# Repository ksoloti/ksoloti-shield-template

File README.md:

# Ksoloti Core Shield Kicad Template

Shield Template Project for Ksoloti Core v0.5+ and Kicad 6+. You can use this as a starting point to design your own shield.

## Installation Instructions

Clone this repo to your User Templates directory. It will then show up under the `User Templates` tab when you create a `New Project from Template`. You can find the default User Templates directory by checking the `KICAD_USER_TEMPLATE_DIR` variable in `Preferences > Configure Paths...` or by navigating to the `User Templates` tab in the Project Template Selector window after you've selected `New Project from Template` in the file menu.

Example Locations (might differ depending on your Kicad version):
 * Windows: `C:\Users\<user name>\Documents\kicad\<version>\template\`
 * Mac: `/Users/<user name>/Documents/kicad/<version>/template/`
 * Linux: `/home/<username>/.local/share/kicad/<version>/template/`

Alternatively, clone the project any location you wish and then browse to it in the `Project Template Selector` window on the `User Templates` tab. 

## About

The Ksoloti Core plugs into the bottom of the template and all its relevant pins are brought out to the sockets of the template.

All pins in this template have been realized as single-pin footprints so you can delete whichever pins you don't need and claim back some space for your design.

The included mounting holes are also optional. You can delete them if they conflict with your part placement (the headers make a solid enough connection), although it is recommended you keep the two top (north) holes to maintain a solid connection when plugging your USB cables. M3 standoffs with 12mm length fit well here.

## Library & Footprints

The template/project has its own little library of parts in case you're looking for something to get started with. Most of these parts are available via Thonk.
* pot, dual pot
* switch, switch with LED, encoder with switch
* 6.35mm TRS audio jack, 3.5mm TRS audio jack
* DIN-5 MIDI socket
* 3mm LED, 3mm bicolor LED (3 pins, AKA)
* 1.3" OLED display (pinout: GND, VCC, SCL, SDA. `BE CAREFUL: pinout varies on these cheap OLEDs! Confirm your OLEDs pinout and adjust the footprint accordingly.`

## Top view

## Bottom view

## Bottom view with Core plugged in

## Parts library

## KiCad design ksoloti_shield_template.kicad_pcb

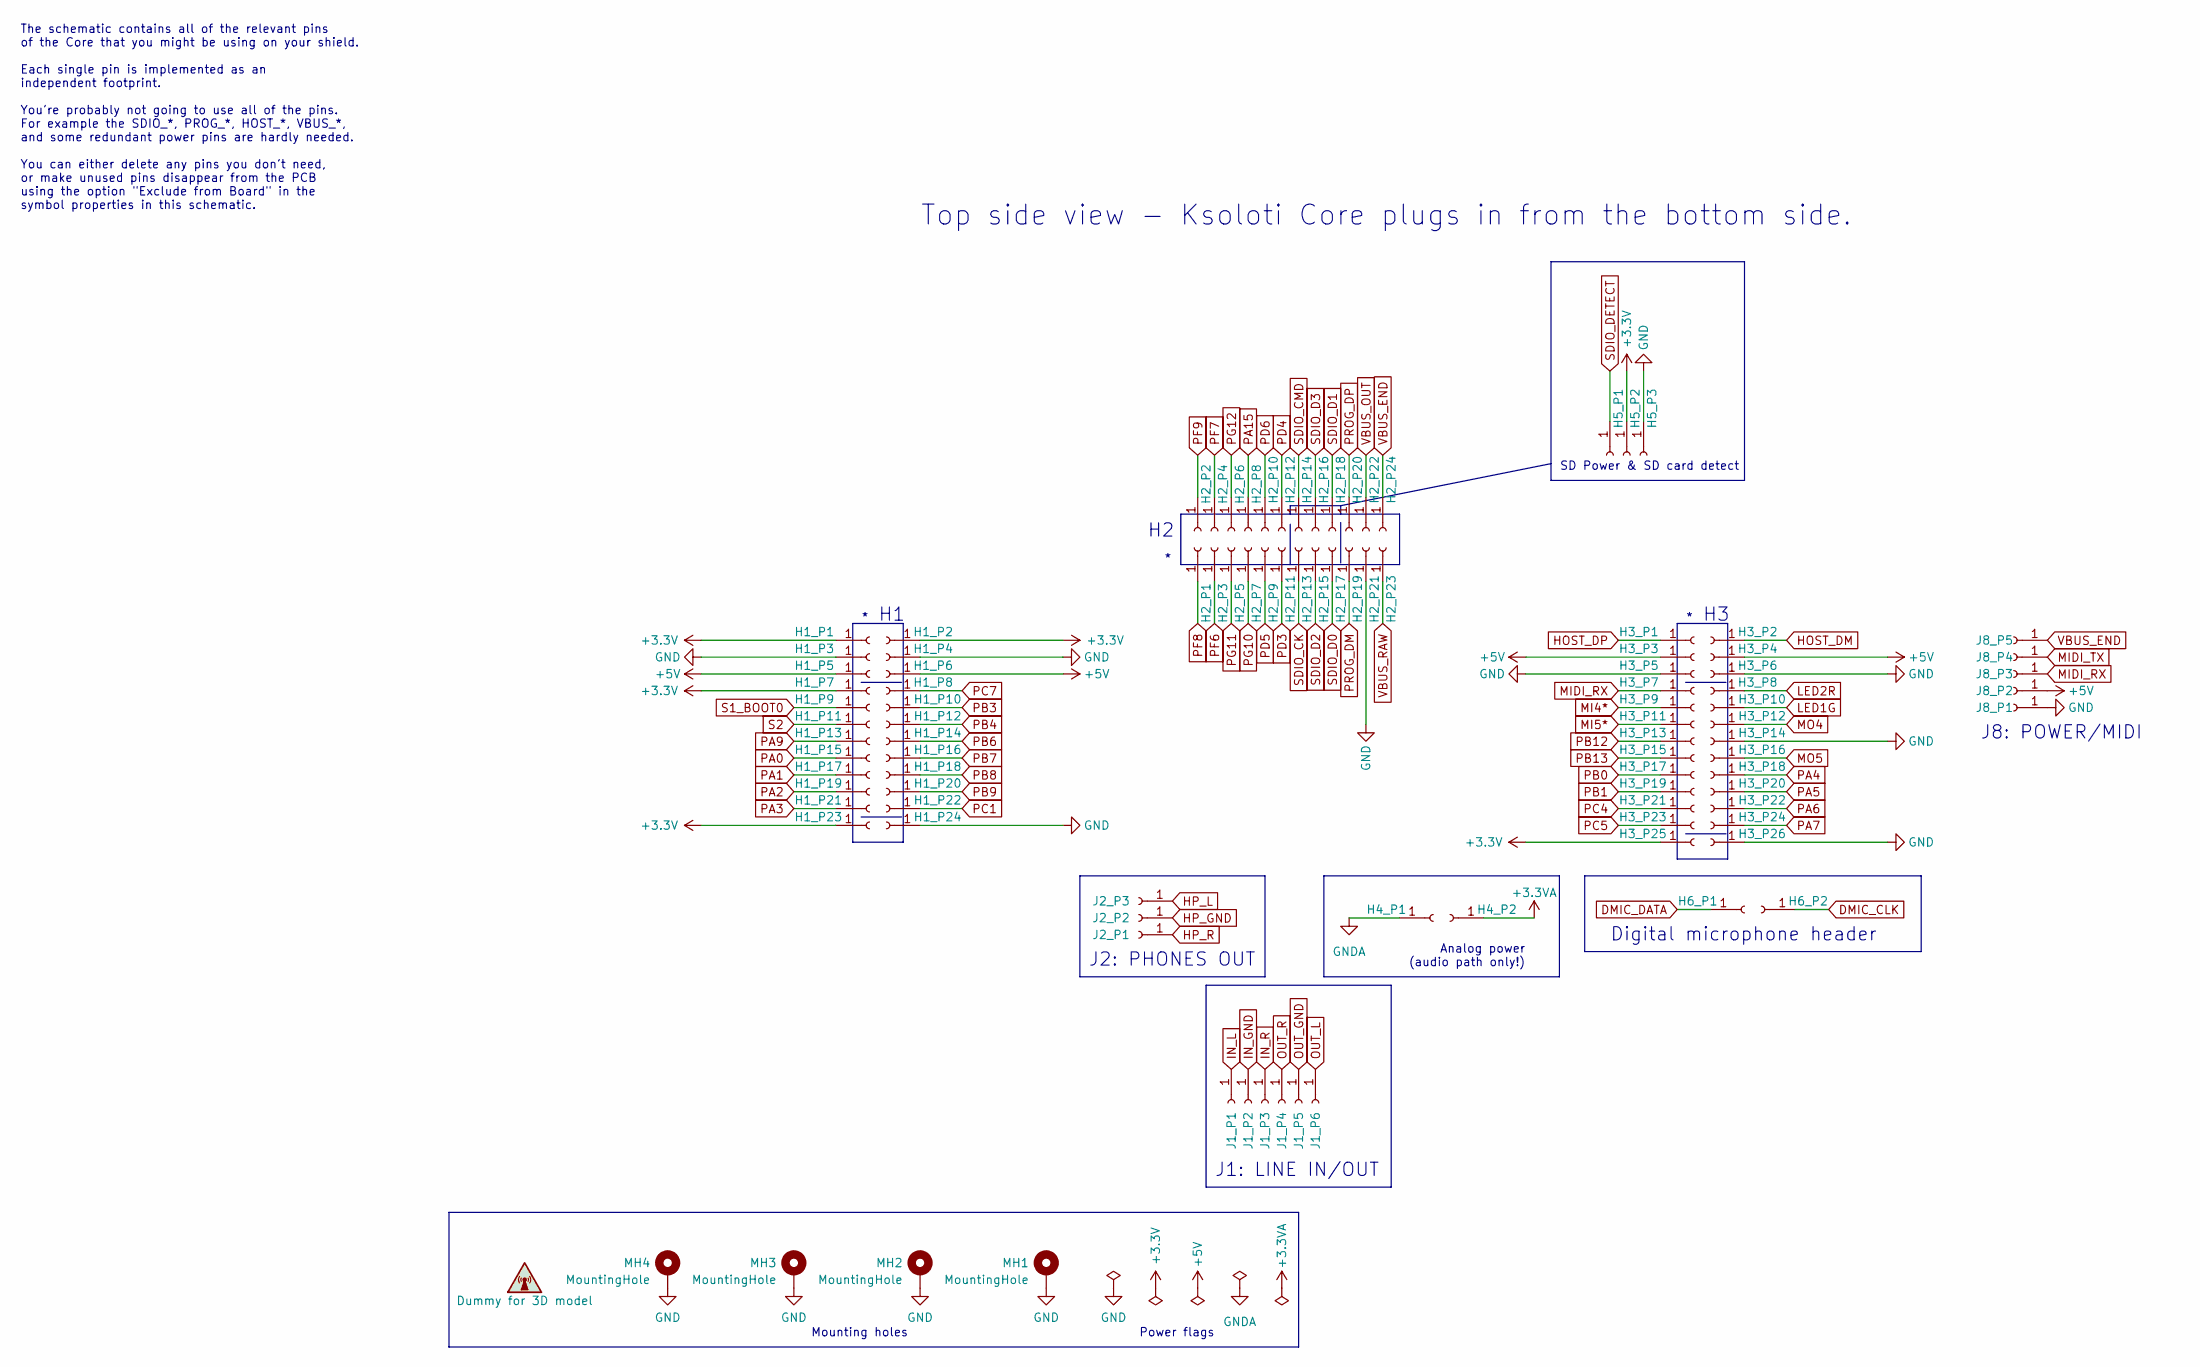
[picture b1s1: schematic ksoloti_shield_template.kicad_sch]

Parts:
DUMMY1: Dummy for 3D model
H1_P1: +3.3V; PinSocket_1x01_P2.54mm_Vertical_smcrt_sqr
H1_P2, H1_P7, H1_P23, H3_P25, H5_P2: +3.3V; PinSocket_1x01_P2.54mm_Vertical_smcrt_round
H1_P3, H1_P4, H1_P24, H2_P21, H3_P5, H3_P6, H3_P14, H3_P26, H5_P3: GND; PinSocket_1x01_P2.54mm_Vertical_smcrt_round
H1_P5, H1_P6, H3_P3, H3_P4: +5V; PinSocket_1x01_P2.54mm_Vertical_smcrt_round
H1_P8: PC7; PinSocket_1x01_P2.54mm_Vertical_smcrt_round
H1_P9: S1_BOOT0; PinSocket_1x01_P2.54mm_Vertical_smcrt_round
H1_P10: PB3; PinSocket_1x01_P2.54mm_Vertical_smcrt_round
H1_P11: S2; PinSocket_1x01_P2.54mm_Vertical_smcrt_round
H1_P12: PB4; PinSocket_1x01_P2.54mm_Vertical_smcrt_round
H1_P13: PA9; PinSocket_1x01_P2.54mm_Vertical_smcrt_round
H1_P14: PB6; PinSocket_1x01_P2.54mm_Vertical_smcrt_round
H1_P15: PA0; PinSocket_1x01_P2.54mm_Vertical_smcrt_round
H1_P16: PB7; PinSocket_1x01_P2.54mm_Vertical_smcrt_round
H1_P17: PA1; PinSocket_1x01_P2.54mm_Vertical_smcrt_round
H1_P18: PB8; PinSocket_1x01_P2.54mm_Vertical_smcrt_round
H1_P19: PA2; PinSocket_1x01_P2.54mm_Vertical_smcrt_round
H1_P20: PB9; PinSocket_1x01_P2.54mm_Vertical_smcrt_round
H1_P21: PA3; PinSocket_1x01_P2.54mm_Vertical_smcrt_round
H1_P22: PC1; PinSocket_1x01_P2.54mm_Vertical_smcrt_round
H2_P1: PF8; PinSocket_1x01_P2.54mm_Vertical_smcrt_sqr
H2_P2: PF9; PinSocket_1x01_P2.54mm_Vertical_smcrt_round
H2_P3: PF6; PinSocket_1x01_P2.54mm_Vertical_smcrt_round
H2_P4: PF7; PinSocket_1x01_P2.54mm_Vertical_smcrt_round
H2_P5: PG11; PinSocket_1x01_P2.54mm_Vertical_smcrt_round
H2_P6: PG12; PinSocket_1x01_P2.54mm_Vertical_smcrt_round
H2_P7: PG10; PinSocket_1x01_P2.54mm_Vertical_smcrt_round
H2_P8: PA15; PinSocket_1x01_P2.54mm_Vertical_smcrt_round
H2_P9: PD5; PinSocket_1x01_P2.54mm_Vertical_smcrt_round
H2_P10: PD6; PinSocket_1x01_P2.54mm_Vertical_smcrt_round
H2_P11: PD3; PinSocket_1x01_P2.54mm_Vertical_smcrt_round
H2_P12: PD4; PinSocket_1x01_P2.54mm_Vertical_smcrt_round
H2_P13: SDIO_CK; PinSocket_1x01_P2.54mm_Vertical_smcrt_round
H2_P14: SDIO_CMD; PinSocket_1x01_P2.54mm_Vertical_smcrt_round
H2_P15: SDIO_D2; PinSocket_1x01_P2.54mm_Vertical_smcrt_round
H2_P16: SDIO_D3; PinSocket_1x01_P2.54mm_Vertical_smcrt_round
H2_P17: SDIO_D0; PinSocket_1x01_P2.54mm_Vertical_smcrt_round
H2_P18: SDIO_D1; PinSocket_1x01_P2.54mm_Vertical_smcrt_round
H2_P19: PROG_DM; PinSocket_1x01_P2.54mm_Vertical_smcrt_round
H2_P20: PROG_DP; PinSocket_1x01_P2.54mm_Vertical_smcrt_round
H2_P22: VBUS_OUT; PinSocket_1x01_P2.54mm_Vertical_smcrt_round
H2_P23: VBUS_RAW; PinSocket_1x01_P2.54mm_Vertical_smcrt_round
H2_P24: VBUS_END; PinSocket_1x01_P2.54mm_Vertical_smcrt_round
H3_P1: HOST_DP; PinSocket_1x01_P2.54mm_Vertical_smcrt_sqr
H3_P2: HOST_DM; PinSocket_1x01_P2.54mm_Vertical_smcrt_round
H3_P7: MIDI_RX; PinSocket_1x01_P2.54mm_Vertical_smcrt_round
H3_P8: LED2R; PinSocket_1x01_P2.54mm_Vertical_smcrt_round
H3_P9: MI4; PinSocket_1x01_P2.54mm_Vertical_smcrt_round
H3_P10: LED1G; PinSocket_1x01_P2.54mm_Vertical_smcrt_round
H3_P11: MI5; PinSocket_1x01_P2.54mm_Vertical_smcrt_round
H3_P12: MO4; PinSocket_1x01_P2.54mm_Vertical_smcrt_round
H3_P13: PB12; PinSocket_1x01_P2.54mm_Vertical_smcrt_round
H3_P15: PB13; PinSocket_1x01_P2.54mm_Vertical_smcrt_round
H3_P16: MO5; PinSocket_1x01_P2.54mm_Vertical_smcrt_round
H3_P17: PB0; PinSocket_1x01_P2.54mm_Vertical_smcrt_round
H3_P18: PA4; PinSocket_1x01_P2.54mm_Vertical_smcrt_round
H3_P19: PB1; PinSocket_1x01_P2.54mm_Vertical_smcrt_round
H3_P20: PA5; PinSocket_1x01_P2.54mm_Vertical_smcrt_round
H3_P21: PC4; PinSocket_1x01_P2.54mm_Vertical_smcrt_round
H3_P22: PA6; PinSocket_1x01_P2.54mm_Vertical_smcrt_round
H3_P23: PC5; PinSocket_1x01_P2.54mm_Vertical_smcrt_round
H3_P24: PA7; PinSocket_1x01_P2.54mm_Vertical_smcrt_round
H4_P1: GNDA; PinSocket_1x01_P2.54mm_Vertical_smcrt_sqr
H4_P2: +3.3VA; PinSocket_1x01_P2.54mm_Vertical_smcrt_round
H5_P1: SDIO_DETECT; PinSocket_1x01_P2.54mm_Vertical_smcrt_sqr
H6_P1: DMIC_DATA; PinSocket_1x01_P2.54mm_Vertical_smcrt_round
H6_P2: DMIC_CLK; PinSocket_1x01_P2.54mm_Vertical_smcrt_round
J1_P1: IN_L; PinSocket_1x01_P2.54mm_Vertical_smcrt_sqr
J1_P2: IN_GND; PinSocket_1x01_P2.54mm_Vertical_smcrt_round
J1_P3: IN_R; PinSocket_1x01_P2.54mm_Vertical_smcrt_round
J1_P4: OUT_R; PinSocket_1x01_P2.54mm_Vertical_smcrt_round
J1_P5: OUT_GND; PinSocket_1x01_P2.54mm_Vertical_smcrt_round
J1_P6: OUT_L; PinSocket_1x01_P2.54mm_Vertical_smcrt_round
J2_P1: HP_R; PinSocket_1x01_P2.54mm_Vertical_smcrt_sqr
J2_P2: HP_GND; PinSocket_1x01_P2.54mm_Vertical_smcrt_round
J2_P3: HP_L; PinSocket_1x01_P2.54mm_Vertical_smcrt_round
J8_P1: GND; PinSocket_1x01_P2.54mm_Vertical_smcrt_sqr
J8_P2: +5V; PinSocket_1x01_P2.54mm_Vertical_smcrt_round
J8_P3: MIDI_RX*; PinSocket_1x01_P2.54mm_Vertical_smcrt_round
J8_P4: MIDI_TX; PinSocket_1x01_P2.54mm_Vertical_smcrt_round
J8_P5: VBUS_END; PinSocket_1x01_P2.54mm_Vertical_smcrt_round
MH1, MH2, MH3, MH4: MountingHole; MountingHole_3.2mm_M3_Pad_Via_tight

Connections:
+3.3V: H1_P1.1, H1_P2.1, H1_P7.1, H1_P23.1, H3_P25.1, H5_P2.1
+3.3VA: H4_P2.1
+5V: H1_P5.1, H1_P6.1, H3_P3.1, H3_P4.1, J8_P2.1
DMIC_CLK: H6_P2.1
DMIC_DATA: H6_P1.1
GND: H1_P3.1, H1_P4.1, H1_P24.1, H2_P21.1, H3_P5.1, H3_P6.1, H3_P14.1, H3_P26.1, H5_P3.1, J8_P1.1, MH1.1, MH2.1, MH3.1, MH4.1
GNDA: H4_P1.1
HOST_DM: H3_P2.1
HOST_DP: H3_P1.1
HP_GND: J2_P2.1
HP_L: J2_P3.1
HP_R: J2_P1.1
IN_GND: J1_P2.1
IN_L: J1_P1.1
IN_R: J1_P3.1
LED1G: H3_P10.1
LED2R: H3_P8.1
MI4*: H3_P9.1
MI5*: H3_P11.1
MIDI_RX: H3_P7.1, J8_P3.1
MIDI_TX: J8_P4.1
MO4: H3_P12.1
MO5: H3_P16.1
OUT_GND: J1_P5.1
OUT_L: J1_P6.1
OUT_R: J1_P4.1
PA0: H1_P15.1
PA1: H1_P17.1
PA2: H1_P19.1
PA3: H1_P21.1
PA4: H3_P18.1
PA5: H3_P20.1
PA6: H3_P22.1
PA7: H3_P24.1
PA9: H1_P13.1
PA15: H2_P8.1
PB0: H3_P17.1
PB1: H3_P19.1
PB3: H1_P10.1
PB4: H1_P12.1
PB6: H1_P14.1
PB7: H1_P16.1
PB8: H1_P18.1
PB9: H1_P20.1
PB12: H3_P13.1
PB13: H3_P15.1
PC1: H1_P22.1
PC4: H3_P21.1
PC5: H3_P23.1
PC7: H1_P8.1
PD3: H2_P11.1
PD4: H2_P12.1
PD5: H2_P9.1
PD6: H2_P10.1
PF6: H2_P3.1
PF7: H2_P4.1
PF8: H2_P1.1
PF9: H2_P2.1
PG10: H2_P7.1
PG11: H2_P5.1
PG12: H2_P6.1
PROG_DM: H2_P19.1
PROG_DP: H2_P20.1
S1_BOOT0: H1_P9.1
S2: H1_P11.1
SDIO_CK: H2_P13.1
SDIO_CMD: H2_P14.1
SDIO_D0: H2_P17.1
SDIO_D1: H2_P18.1
SDIO_D2: H2_P15.1
SDIO_D3: H2_P16.1
SDIO_DETECT: H5_P1.1
VBUS_END: H2_P24.1, J8_P5.1
VBUS_OUT: H2_P22.1
VBUS_RAW: H2_P23.1

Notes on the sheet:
J2: PHONES OUT
The schematic contains all of the relevant pins of the Core that you might be using on your shield. Each single pin is implemented as an independent footprint. You're probably not going to use all of the pins. For example the SDIO_*, PROG_*, HOST_*, VBUS_*, and some redundant power pins are hardly 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
J8: POWER/MIDI
Mounting holes
Top side view - Ksoloti Core plugs in from the bottom side.
Power flags
SD Power & SD card detect
Analog power (audio path only!)
J1: LINE IN/OUT
Digital microphone header

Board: 4 copper layers, 101 parts (101 on the bottom side), 5 nets, no tracks yet.

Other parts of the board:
G513513: LOGO

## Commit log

2023-12-23 Add images
2023-12-23 Create LICENSE
2023-12-23 Added required files for proper Kicad User Template
2023-12-23 Updated README with install instructions
2023-12-23 Added alternative install instructions
2023-12-24 small edits to template merge
2023-12-24 fix headings
2023-12-24 add a selection of symbols and footprints to start out with: pots, switches, encoder, jacks, LEDs, OLED ...
2023-12-24 fix accidental placement of random footprints
2023-12-24 fix nrj6hf symbol: was dual
2023-12-24 add 3mm LED and 3mm bicolor LED symbols&footprints
2023-12-24 add parts screenshot
2024-05-04 edit 3d model
